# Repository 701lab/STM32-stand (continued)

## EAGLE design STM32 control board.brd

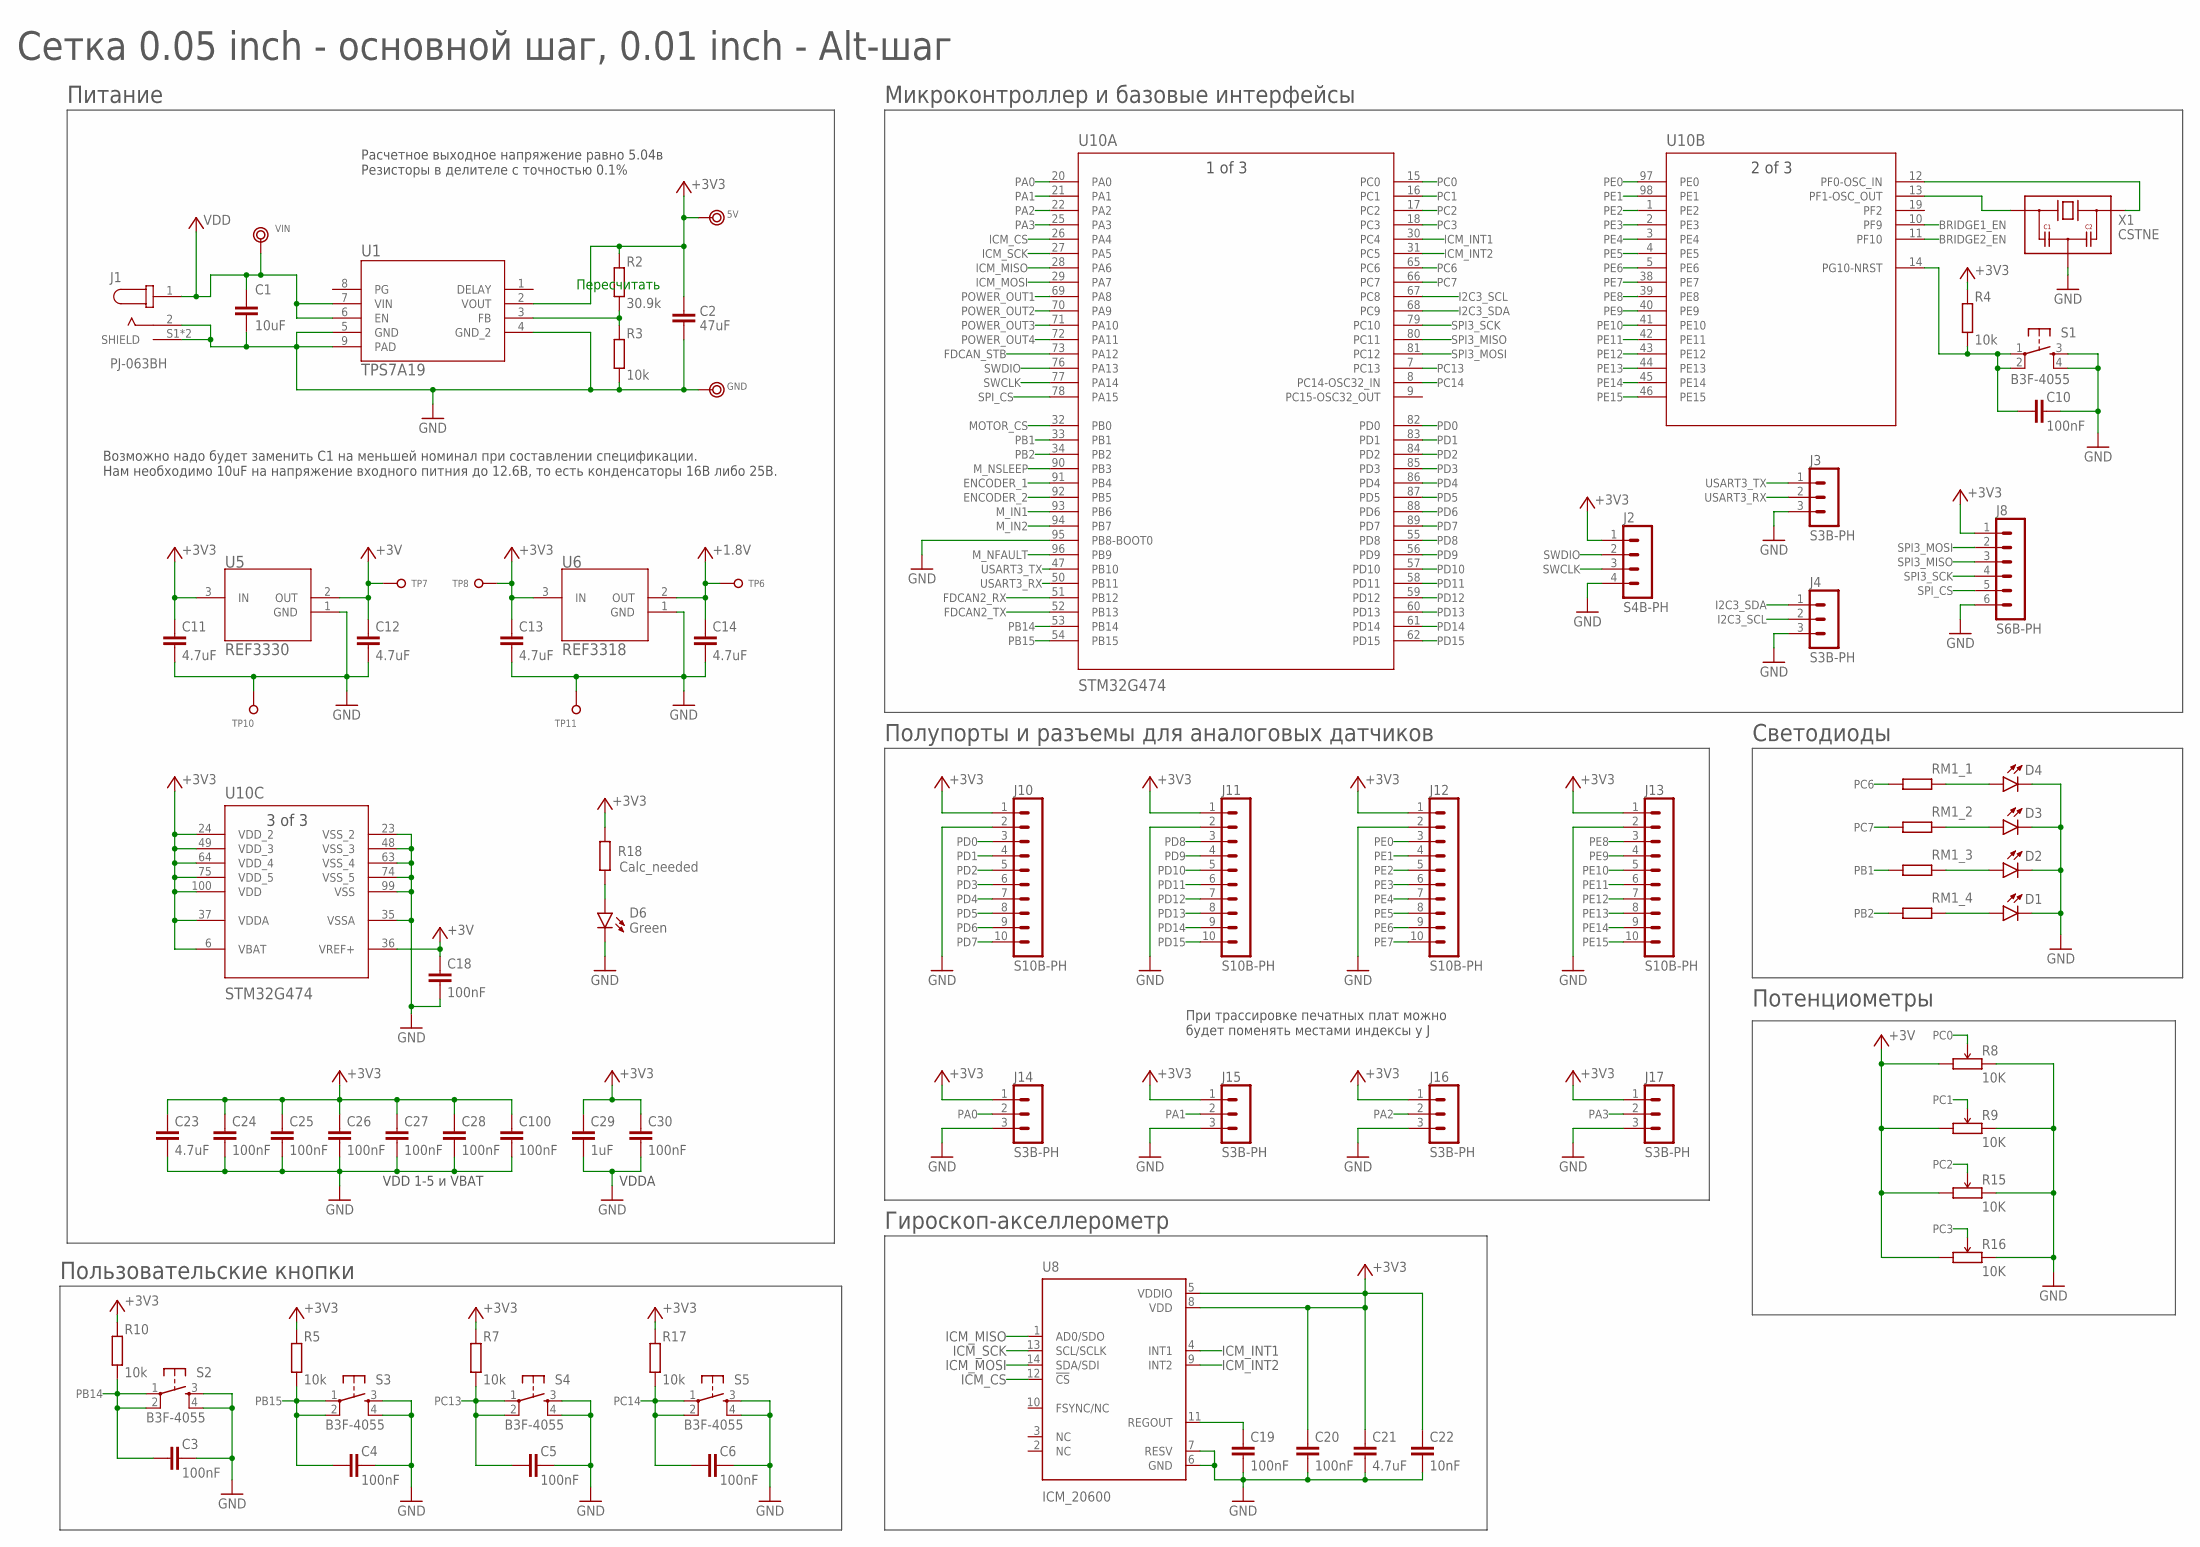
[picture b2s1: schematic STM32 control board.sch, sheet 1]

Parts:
5V: TEST_RING
C1: 10uF; C1206
C2: 47uF; C1210; MANUFACTURER_PART_NUMBER GRM32ER61C476ME15L
C3, C4, C5, C6, C10, C18, C19, C20, C24, C25, C26, C27, C28, C30, C100: 100nF; C0402
C11, C12, C13, C14, C21, C23: 4.7uF; C0603
C22: 10nF; C0402
C29: 1uF; C0402
D1, D2, D3, D4: Blue; LED-0805
D6: Green; LED-0805
GND: TEST_RING
J1: PJ-063BH; CUI_PJ-063BH
J2: S4B-PH; S4B-PH-K
J3, J4, J14, J15, J16, J17: S3B-PH; S3B-PH-K
J8: S6B-PH; S6B-PH-K
J10, J11, J12, J13: S10B-PH; S10B-PH-K
R2: 30.9k; R0402
R3, R4, R5, R7, R10, R17: 10k; R0402
R8, R9, R15, R16: 10K; ALPS_PTM
R18: Calc_needed; R0402
RM1: RES_ARRAY; 0603-ARC
S1, S2, S3, S4, S5: B3F-4055; SWITCH_B3F-4055
TP6: 1.8; TP1.27MM_MASK_SILKSCREEN
TP7: 3.0; TP1.27MM_MASK_SILKSCREEN
TP8: 3.3; TP1.27MM_MASK_SILKSCREEN
TP10, TP11: TEST_PAD-[1.27MM_SK]; TP1.27MM_MASK_SILKSCREEN
U1: TPS7A19; DRB0008B
U5: REF3330; SOT-23-3
U6: REF3318; SOT-23-3
U8: ICM_20600; 14_PIN_LGA
U10: STM32G474; LPQFP-100
VIN: TEST_RING
X1: CSTNE; MURATA_SMD_3P

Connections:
+1.8V: C14.1, TP6.1, U6.2 (OUT); also elsewhere on the board
+3V: C12.1, C18.1, R8.P$1 (1), R9.P$1 (1), R15.P$1 (1), R16.P$1 (1), TP7.1, U5.2 (OUT), U10.36 (VREF+)
+3V3: 5V.1, C2.1, C11.1, C13.1, C20.1, C21.1, C22.1, C23.1, C24.1, C25.1, C26.1, C27.1, C28.1, C29.1, C30.1, C100.1, J2.1, J8.1, J10.1, J11.1, J12.1, J13.1, J14.1, J15.1, J16.1, J17.1, R2.2, R4.1, R5.2, R7.2, R10.2, R17.2, R18.2, TP8.1, U1.2 (VOUT), U5.3 (IN), U6.3 (IN), U8.5 (VDDIO), U8.8 (VDD), U10.6 (VBAT), U10.24 (VDD_2), U10.37 (VDDA), U10.49 (VDD_3), U10.64 (VDD_4), U10.75 (VDD_5), U10.100 (VDD); also elsewhere on the board
BRIDGE1_EN: U10.10 (PF9); also elsewhere on the board
BRIDGE2_EN: U10.11 (PF10); also elsewhere on the board
ENCODER_1: U10.91 (PB4); also elsewhere on the board
ENCODER_2: U10.92 (PB5); also elsewhere on the board
FDCAN2_RX: U10.51 (PB12)
FDCAN2_TX: U10.52 (PB13)
FDCAN_STB: U10.73 (PA12)
GND: C1.2, C2.2, C3.2, C4.2, C5.2, C6.2, C10.2, C11.2, C12.2, C13.2, C14.2, C18.2, C19.2, C20.2, C21.2, C22.2, C23.2, C24.2, C25.2, C26.2, C27.2, C28.2, C29.2, C30.2, C100.2, D1.- (C), D2.- (C), D3.- (C), D4.- (C), D6.- (C), GND.1, J1.2, J1.S1 (SHIELD), J1.S2 (SHIELD), J2.4, J3.3, J4.3, J8.6, J10.2, J11.2, J12.2, J13.2, J14.3, J15.3, J16.3, J17.3, R3.1, R8.P$3 (3), R9.P$3 (3), R15.P$3 (3), R16.P$3 (3), S1.3, S1.4, S2.3, S2.4, S3.3, S3.4, S4.3, S4.4, S5.3, S5.4, TP10.1, TP11.1, U1.4 (GND_2), U1.5 (GND), U1.9 (PAD), U5.1 (GND), U6.1 (GND), U8.6 (GND), U8.7 (RESV), U10.23 (VSS_2), U10.35 (VSSA), U10.48 (VSS_3), U10.63 (VSS_4), U10.74 (VSS_5), U10.95 (PB8-BOOT0), U10.99 (VSS), X1.2 (GND); also elsewhere on the board
I2C3_SCL: J4.2, U10.67 (PC8)
I2C3_SDA: J4.1, U10.68 (PC9)
ICM_CS: U8.12 (!CS), U10.26 (PA4)
ICM_INT1: U8.4 (INT1), U10.30 (PC4)
ICM_INT2: U8.9 (INT2), U10.31 (PC5)
ICM_MISO: U8.1 (AD0/SDO), U10.28 (PA6)
ICM_MOSI: U8.14 (SDA/SDI), U10.29 (PA7)
ICM_SCK: U8.13 (SCL/SCLK), U10.27 (PA5)
MOTOR_CS: U10.32 (PB0); also elsewhere on the board
M_IN1: U10.93 (PB6); also elsewhere on the board
M_IN2: U10.94 (PB7); also elsewhere on the board
M_NFAULT: U10.96 (PB9); also elsewhere on the board
M_NSLEEP: U10.90 (PB3); also elsewhere on the board
unnamed: U10.12 (PF0-OSC_IN), X1.3 (OUT)
unnamed: U10.13 (PF1-OSC_OUT), X1.1 (IN)
unnamed: D1.+ (A), RM1.5 (2)
unnamed: D2.+ (A), RM1.6 (2)
unnamed: D3.+ (A), RM1.7 (2)
unnamed: D6.+ (A), R18.1
unnamed: D4.+ (A), RM1.8 (2)
unnamed: R2.1, R3.2, U1.3 (FB)
PA0: J14.2, U10.20 (PA0)
PA1: J15.2, U10.21 (PA1)
PA2: J16.2, U10.22 (PA2)
PA3: J17.2, U10.25 (PA3)
PB1: RM1.3 (1), U10.33 (PB1)
PB2: RM1.4 (1), U10.34 (PB2)
PB14: C3.1, R10.1, S2.1, S2.2, U10.53 (PB14)
PB15: C4.1, R5.1, S3.1, S3.2, U10.54 (PB15)
PC0: R8.P$2 (2), U10.15 (PC0)
PC1: R9.P$2 (2), U10.16 (PC1)
PC2: R15.P$2 (2), U10.17 (PC2)
PC3: R16.P$2 (2), U10.18 (PC3)
PC6: RM1.1, U10.65 (PC6)
PC7: RM1.2 (1), U10.66 (PC7)
PC13: C5.1, R7.1, S4.1, S4.2, U10.7 (PC13)
PC14: C6.1, R17.1, S5.1, S5.2, U10.8 (PC14-OSC32_IN)
PD0: J10.3, U10.82 (PD0)
PD1: J10.4, U10.83 (PD1)
PD2: J10.5, U10.84 (PD2)
PD3: J10.6, U10.85 (PD3)
PD4: J10.7, U10.86 (PD4)
PD5: J10.8, U10.87 (PD5)
PD6: J10.9, U10.88 (PD6)
PD7: J10.10, U10.89 (PD7)
PD8: J11.3, U10.55 (PD8)
PD9: J11.4, U10.56 (PD9)
PD10: J11.5, U10.57 (PD10)
PD11: J11.6, U10.58 (PD11)
PD12: J11.7, U10.59 (PD12)
PD13: J11.8, U10.60 (PD13)
PD14: J11.9, U10.61 (PD14)
PD15: J11.10, U10.62 (PD15)
PE0: J12.3, U10.97 (PE0)
PE1: J12.4, U10.98 (PE1)
PE2: J12.5, U10.1 (PE2)
PE3: J12.6, U10.2 (PE3)
PE4: J12.7, U10.3 (PE4)
PE5: J12.8, U10.4 (PE5)
PE6: J12.9, U10.5 (PE6)
PE7: J12.10, U10.38 (PE7)
PE8: J13.3, U10.39 (PE8)
PE9: J13.4, U10.40 (PE9)
PE10: J13.5, U10.41 (PE10)
PE11: J13.6, U10.42 (PE11)
PE12: J13.7, U10.43 (PE12)
PE13: J13.8, U10.44 (PE13)
PE14: J13.9, U10.45 (PE14)
PE15: J13.10, U10.46 (PE15)
POWER_OUT1: U10.69 (PA8); also elsewhere on the board
POWER_OUT2: U10.70 (PA9); also elsewhere on the board
POWER_OUT3: U10.71 (PA10); also elsewhere on the board
POWER_OUT4: U10.72 (PA11); also elsewhere on the board
REG: C19.1, U8.11 (REGOUT)
RST: C10.1, R4.2, S1.1, S1.2, U10.14 (PG10-NRST)
SPI3_MISO: J8.3, U10.80 (PC11)
SPI3_MOSI: J8.2, U10.81 (PC12)
SPI3_SCK: J8.4, U10.79 (PC10)
SPI_CS: J8.5, U10.78 (PA15)
SWCLK: J2.3, U10.77 (PA14)
SWDIO: J2.2, U10.76 (PA13)
USART3_RX: J3.2, U10.50 (PB11)
USART3_TX: J3.1, U10.47 (PB10)
VDD: C1.1, J1.1, U1.6 (EN), U1.7 (VIN), VIN.1; also elsewhere on the board

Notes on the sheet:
Сетка 0.05 inch - основной шаг, 0.01 inch - Alt-шаг
При трассировке печатных плат можно будет поменять местами индексы у J
VDD 1-5 и VBAT
VDDA
Расчетное выходное напряжение равно 5.04в Резисторы в делителе с точностью 0.1%
Возможно надо будет заменить С1 на меньшей номинал при составлении спецификации. Нам необходимо 10uF на напряжение входного питния до 12.6В, то есть конденсаторы 16В либо 25В.
Микроконтроллер и базовые интерфейсы
Полупорты и разъемы для аналоговых датчиков
Светодиоды
Питание
Потенциометры
Пользовательские кнопки
Пересчитать
Гироскоп-акселлерометр

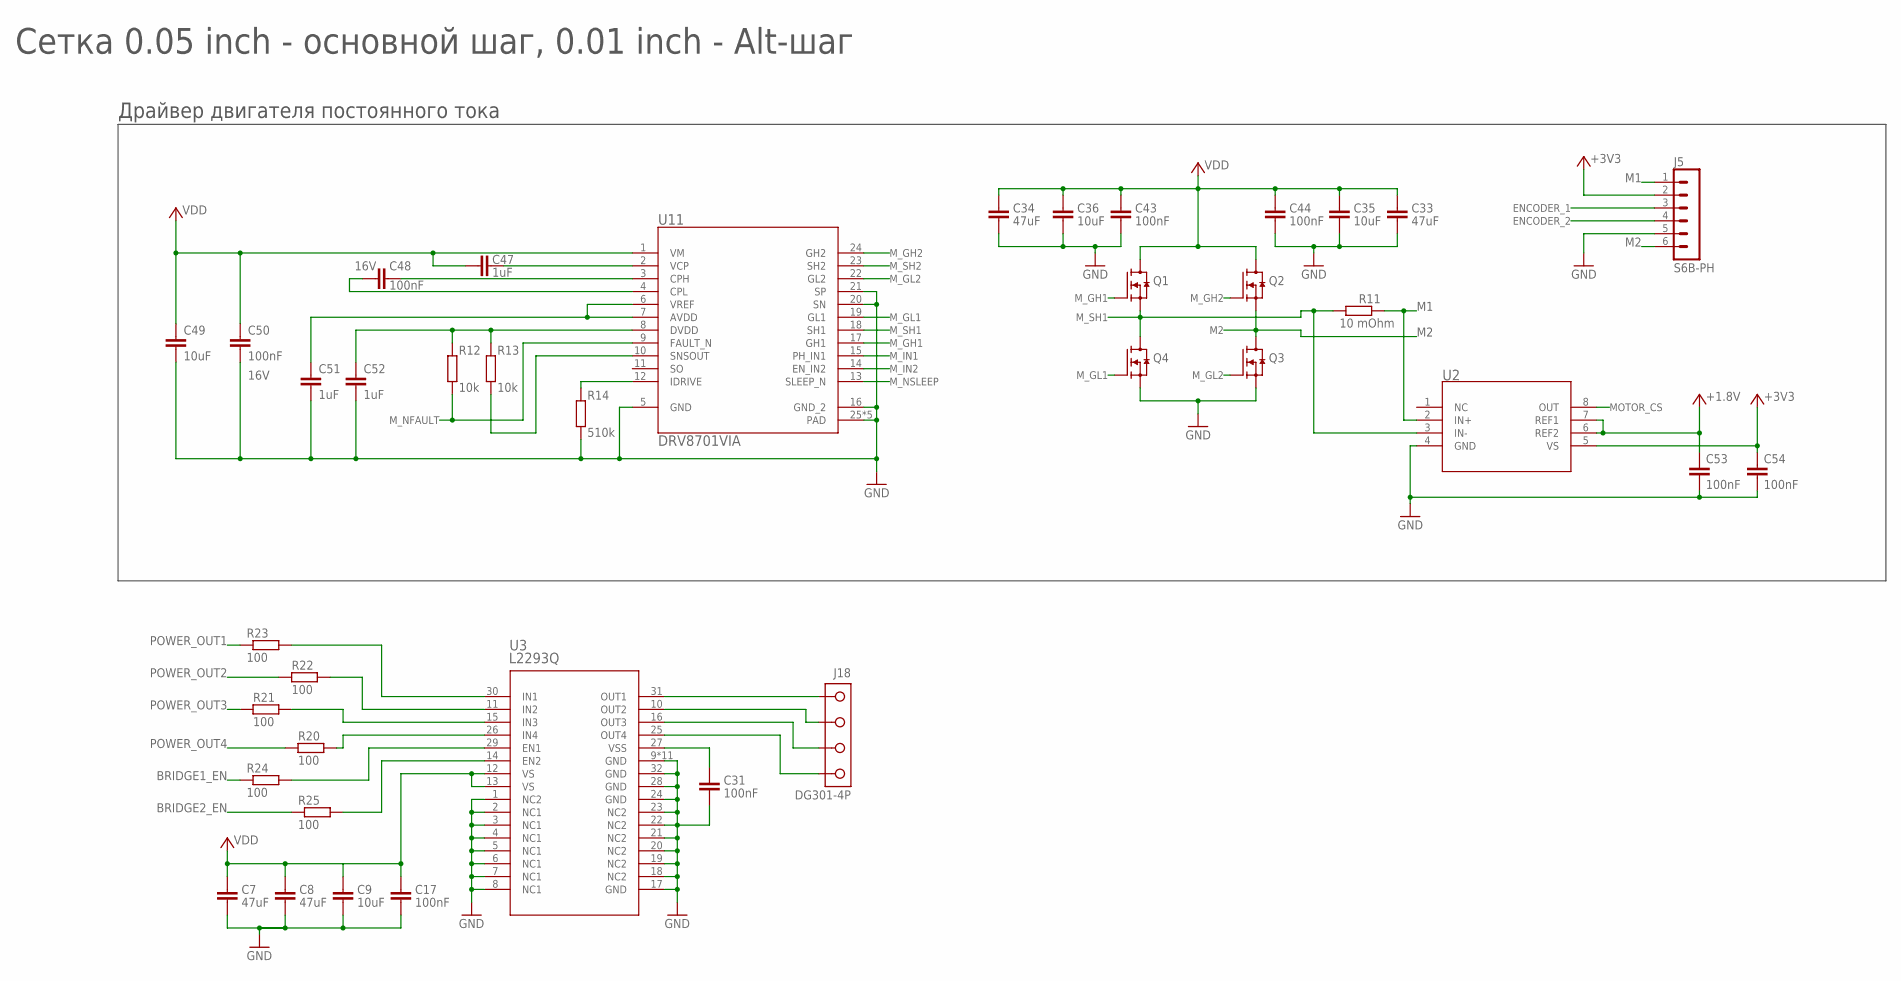
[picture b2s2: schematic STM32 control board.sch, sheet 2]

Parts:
C7, C8, C33, C34: 47uF; C1210; MANUFACTURER_PART_NUMBER GRM32ER61C476ME15L
C9, C35, C36: 10uF; C1206; MANUFACTURER_PART_NUMBER CL31B106KOHNNNE
C17, C31, C53, C54: 100nF; C0402
C43, C44, C48, C50: 100nF; C0603
C47: 1uF; C0603
C49: 10uF; C1206
C51, C52: 1uF; C0402
J5: S6B-PH; S6B-PH-K
J18: DG301-4P
Q1, Q2, Q3, Q4: CSD15571Q2; SON2X2
R11: 10 mOhm; CS_R0805; MANUFACTURER_PART_NUMBER STE0805MW75R010F
R12, R13: 10k; R0402
R14: 510k; R0402
R20, R21, R22, R23, R24, R25: 100; R0402
U2: INA240_TSSOP; TSSOP-8; MANUFACTURER_PART_NUMBER INA240
U3: L2293Q; QFN_293Q_STM
U11: DRV8701VIA; VQFN-24-VIA

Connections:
+1.8V: C53.1, U2.6 (REF2), U2.7 (REF1); also elsewhere on the board
+3V3: C54.1, J5.2, U2.5 (VS); also elsewhere on the board
AVDD1: C51.2, U11.6 (VREF), U11.7 (AVDD)
BRIDGE1_EN: R24.1; also elsewhere on the board
BRIDGE2_EN: R25.1; also elsewhere on the board
DRV2_SNSOUT: R13.1, U11.10 (SNSOUT)
DVDD2: C52.2, R12.2, R13.2, U11.8 (DVDD)
ENCODER_1: J5.3; also elsewhere on the board
ENCODER_2: J5.4; also elsewhere on the board
GND: C7.2, C8.2, C9.2, C17.2, C31.2, C33.2, C34.2, C35.2, C36.2, C43.2, C44.2, C49.2, C50.2, C51.1, C52.1, C53.2, C54.2, J5.5, Q3.S4 (S), Q3.S8 (S), Q4.S4 (S), Q4.S8 (S), R14.1, U2.4 (GND), U3.1 (NC2), U3.2 (NC1), U3.3 (NC1), U3.4 (NC1), U3.5 (NC1), U3.6 (NC1), U3.7 (NC1), U3.8 (NC1), U3.9 (GND), U3.17 (GND), U3.18 (NC2), U3.19 (NC2), U3.20 (NC2), U3.21 (NC2), U3.22 (NC2), U3.23 (NC2), U3.24 (GND), U3.28 (GND), U3.32 (GND), U3.P$1 (GND), U3.P$2 (GND), U3.P$3 (GND), U3.P$4 (GND), U3.P$5 (GND), U3.P$6 (GND), U3.P$7 (GND), U3.P$8 (GND), U3.P$9 (GND), U3.PAD (GND), U11.5 (GND), U11.16 (GND_2), U11.20 (SN), U11.21 (SP), U11.25 (PAD), U11.26 (PAD), U11.27 (PAD), U11.28 (PAD), U11.29 (PAD); also elsewhere on the board
M1: J5.1, R11.2, U2.2 (IN+)
M2: J5.6, Q2.S4 (S), Q2.S8 (S), Q3.D1 (D), Q3.D2 (D), Q3.D5 (D), Q3.D6 (D), Q3.D7 (D)
MOTOR_CS: U2.8 (OUT); also elsewhere on the board
M_GH1: Q1.G3 (G), U11.17 (GH1)
M_GH2: Q2.G3 (G), U11.24 (GH2)
M_GL1: Q4.G3 (G), U11.19 (GL1)
M_GL2: Q3.G3 (G), U11.22 (GL2)
M_IN1: U11.15 (PH_IN1); also elsewhere on the board
M_IN2: U11.14 (EN_IN2); also elsewhere on the board
M_NFAULT: R12.1, U11.9 (FAULT_N); also elsewhere on the board
M_NSLEEP: U11.13 (SLEEP_N); also elsewhere on the board
M_SH1: Q1.S4 (S), Q1.S8 (S), Q4.D1 (D), Q4.D2 (D), Q4.D5 (D), Q4.D6 (D), Q4.D7 (D), R11.1, U2.3 (IN-), U11.18 (SH1)
M_SH2: U11.23 (SH2)
unnamed: R23.2, U3.30 (IN1)
unnamed: R22.2, U3.11 (IN2)
unnamed: R21.2, U3.15 (IN3)
unnamed: C31.1, U3.27 (VSS)
unnamed: R20.2, U3.26 (IN4)
unnamed: R24.2, U3.29 (EN1)
unnamed: R25.2, U3.14 (EN2)
unnamed: C48.1, U11.3 (CPH)
unnamed: C48.2, U11.4 (CPL)
unnamed: C47.2, U11.2 (VCP)
unnamed: R14.2, U11.12 (IDRIVE)
POUT1: J18.1, U3.31 (OUT1)
POUT2: J18.2, U3.10 (OUT2)
POUT3: J18.3, U3.16 (OUT3)
POUT4: J18.4, U3.25 (OUT4)
POWER_OUT1: R23.1; also elsewhere on the board
POWER_OUT2: R22.1; also elsewhere on the board
POWER_OUT3: R21.1; also elsewhere on the board
POWER_OUT4: R20.1; also elsewhere on the board
VDD: C7.1, C8.1, C9.1, C17.1, C33.1, C34.1, C35.1, C36.1, C43.1, C44.1, C47.1, C49.1, C50.1, Q1.D1 (D), Q1.D2 (D), Q1.D5 (D), Q1.D6 (D), Q1.D7 (D), Q2.D1 (D), Q2.D2 (D), Q2.D5 (D), Q2.D6 (D), Q2.D7 (D), U3.12 (VS), U3.13 (VS), U11.1 (VM); also elsewhere on the board

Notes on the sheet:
Сетка 0.05 inch - основной шаг, 0.01 inch - Alt-шаг
16V
Драйвер двигателя постоянного тока

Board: 2 copper layers, 113 parts (0 on the bottom side), 117 nets, no tracks yet.

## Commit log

2020-07-04 Basic shematic creation
2020-07-09 Update STM32 control board.sch
    Review
2020-07-09 Update eagle.epf
    Review
2020-07-09 changed power diode position
2020-07-10 power_output_design_in_progress
2020-07-12 board created
2020-07-13 Placed connectors as i see
2020-07-13 Files reorganization
2020-07-13 renumbered schematic
2020-07-16 Can removed
2020-07-19 for BOM review
2020-07-26 components placement for review
2020-07-26 cutout fixes
2020-07-26 Not finished consept
2020-07-27 consept update
2020-07-28 placement fixes.
    Current size is 104*120mm
2020-07-29 routing
2020-07-29 screw terminal placement fix
2020-07-29 routing part 2
2020-07-29 routing part 3
2020-07-30 polygons part 1
2020-08-01 for routing rewiew
2020-08-11 added stiching vias
2020-08-11 small gnd plane fix
2020-08-13 fixed position of power jack
2020-08-14 3d model updated
2020-08-14 Added some changes to routing
2020-08-15 silkscreen
2020-08-19 silkscreen first time uploaded
2020-08-20 Silkscreen for rewiew
2020-08-21 Documentation for rewiew
2020-08-22 Addded drill file
2020-08-22 added zip file with gerbers
2020-08-24 silckscreen fixes after rewiew
2020-09-11 board file
2020-10-15 ESCD
2021-01-14 Updated the README and added schematics
2021-01-14 Added the forgotten schematic
